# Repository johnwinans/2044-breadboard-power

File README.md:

# 2044-breadboard-power V3
Power supply for a breadboard.

These are the source files for a KiCad project featured in a tutorial here:

https://www.youtube.com/playlist?list=PL3by7evD3F51fKkyrUbH-PCdwPCWc9F8a

If you want to make one of these for yourself you can use this design as
it is or and alter it and make it better.  

If you just want one, see the PDF file for the digikey order IDs of the parts
and here is a place where you can order 3 of these (bare boards) for $6.30 
including shipping (I don't get a penny of that by the way.  I just think it 
is a decent deal):

https://oshpark.com/shared_projects/D6qLABBx

Here are some images of the release V3 (USB-powered) board:

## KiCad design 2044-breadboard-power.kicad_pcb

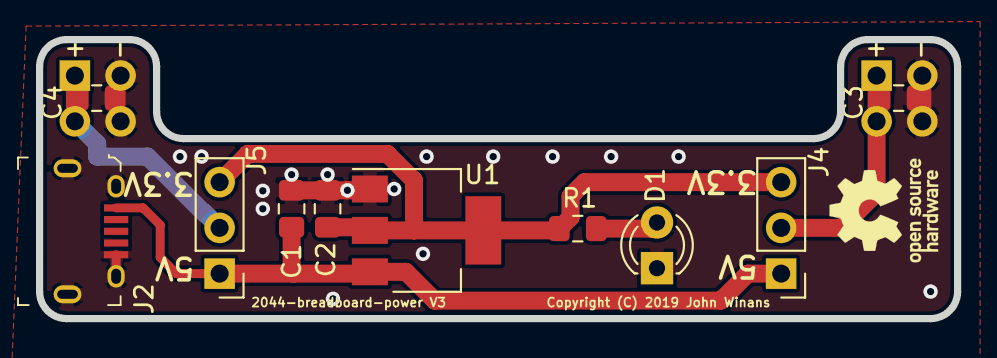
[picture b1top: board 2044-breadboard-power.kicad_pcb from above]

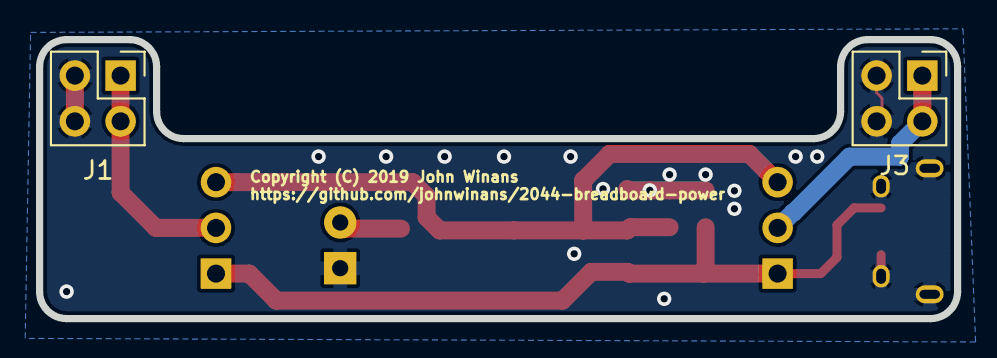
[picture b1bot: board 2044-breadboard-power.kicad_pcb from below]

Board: 2 copper layers, 51.0 x 15.5 mm, 12 parts (2 on the bottom side), 6 nets.

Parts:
C1: 10uF; C_0805_2012Metric_Pad1.15x1.40mm_HandSolder
C2, C3, C4: 22uF; C_0805_2012Metric_Pad1.15x1.40mm_HandSolder
D1: LED_ALT; LED_D3.0mm
J1, J3: Conn_02x02_Odd_Even; PinHeader_2x02_P2.54mm_Vertical
J2: 10118194-0001LF; USB_Micro_B_Female_10118194-0001LF
J4, J5: Conn_01x03; PinHeader_1x03_P2.54mm_Vertical
R1: 330; R_0805_2012Metric_Pad1.15x1.40mm_HandSolder
U1: AZ1117CH-3.3TRG1; SOT-223-3_TabPin2

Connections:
+3V3: C2.1, J4.3, J5.3, R1.1, U1.2
+5V: C1.1, J2.1, J4.1, J5.1, U1.3
/Vout1: C3.1, J1.1, J1.2, J4.2
/Vout2: C4.1, J3.1, J3.2, J5.2
GND: C1.2, C2.2, C3.2, C4.2, D1.1, J1.3, J1.4, J2.5, J2.SH, J3.3, J3.4, U1.1
unnamed: D1.2, R1.2

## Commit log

2019-02-10 Initial project import.
2019-02-10 Link to the YouTube tutorial describing this project.
2019-02-11 Change power connector to USB & remove 5V reg.
2019-02-13 Fix typo in solder mask width value.
2019-02-13 Add images for github README file.
2019-02-13 Added images of the PCB.
2019-02-17 Add link to pshpark if you want to order one of my design.
2019-02-17 Add warning about untested design.
2019-02-17 Fix formating.
2019-02-21 Add digikey number for J2.
2019-02-25 Fixed the wrong Digikey part number for J2.
2019-02-27 Add ground on the output headers.
2019-02-27 Copy over from v2.1.
2019-02-27 Fix link to oshpark V3 project release.
2019-03-12 Board received and tested OK. Removed warning.

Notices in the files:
2044-breadboard-power.kicad_pcb:
Copyright (C) 2019 John Winans
